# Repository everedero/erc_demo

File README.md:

# KiCAD ERC demos

Catastrophic schematics made to demonstrate why ERC exists, and how to use them.

Current KiCAD version used: V8

Also see exemple in [asynthosc](https://github.com/everedero/asynth2osc/tree/broken_erc).

## KiCAD ERC saving the day

* Get to know them!

### Mainstream ERC: the ones people really use
* Unresolved text variables and "software" bugs
* Issues with libraries
* "No connect" and no connect indicator

### Misunderstood ERC: are they really useful?
* Grid: not respecting the grid is a big trap
* 4 connection points: can be legit but can also be a graphical trap
* Footprints and footprints filters

### Really misundesrstood ERC: the connection matrix
* Some external components do not have pin types set: check and repair components

### For people who want several net names per net
KiCAD compiles nets and ends up choosing a single name per net in the netlist, aka internal
 representation of the schematics, the one you will find in PCB view.

This means that it does not like nets with several labels, it will randomly choose one, and
it will complain about that:
* Both uC2\_4 and GPIO35 are attached to the same items, GPIO35 will be used in the netlist

If the net connects to a bus, it will trigger issue because belonging to bus depends on the net.
With previous exemple, if the bus is uC2\_[0..5], uc2\_4 belongs to it but not GPIO35. However,
KiCAD decided to name the net GPIO35.
* GPIO35 graphically connected but not a member of a bus

If you want a diff pair, KiCAD also relies on net names, so the names have to be "toto\_P" and
"toto\_N" (or "toto+" and "toto-").

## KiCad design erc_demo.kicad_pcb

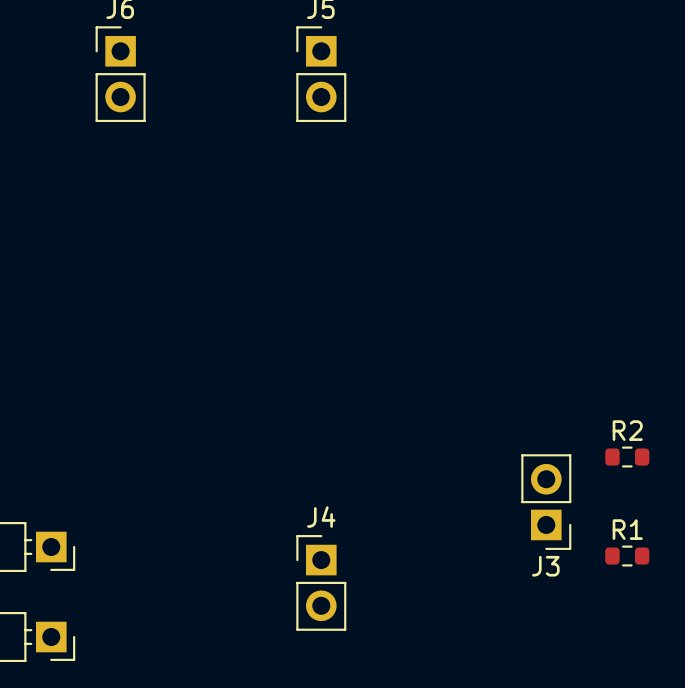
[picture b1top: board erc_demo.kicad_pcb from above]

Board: 2 copper layers, 8 parts (0 on the bottom side), 6 nets, no tracks yet.

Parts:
J1, J2: Conn_01x01; PinHeader_1x01_P2.54mm_Horizontal
J3, J4, J5, J6: Conn_01x02; PinHeader_1x02_P2.54mm_Vertical
R1, R2: R; R_0603_1608Metric

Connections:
+3V3: J3.2, R2.1
/Daughter sheet/TOTO: J5.1, J6.1
/NAME_IN_TOPLEVEL: J5.2, J6.2
/USB_M: J1.1, J4.1
/USB_P: J2.1, J4.2
GND: J3.1, R1.2

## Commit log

2025-11-10 doc: link to broken project exemple
2025-11-10 doc: update
2025-11-10 doc: add list of erc
2025-11-13 feat: add a hierarchy name demo
2025-11-13 feat: kicad9 scheets updated
